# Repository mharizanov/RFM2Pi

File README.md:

RFM2Pi
======

RFM12B to Raspberry Pi board

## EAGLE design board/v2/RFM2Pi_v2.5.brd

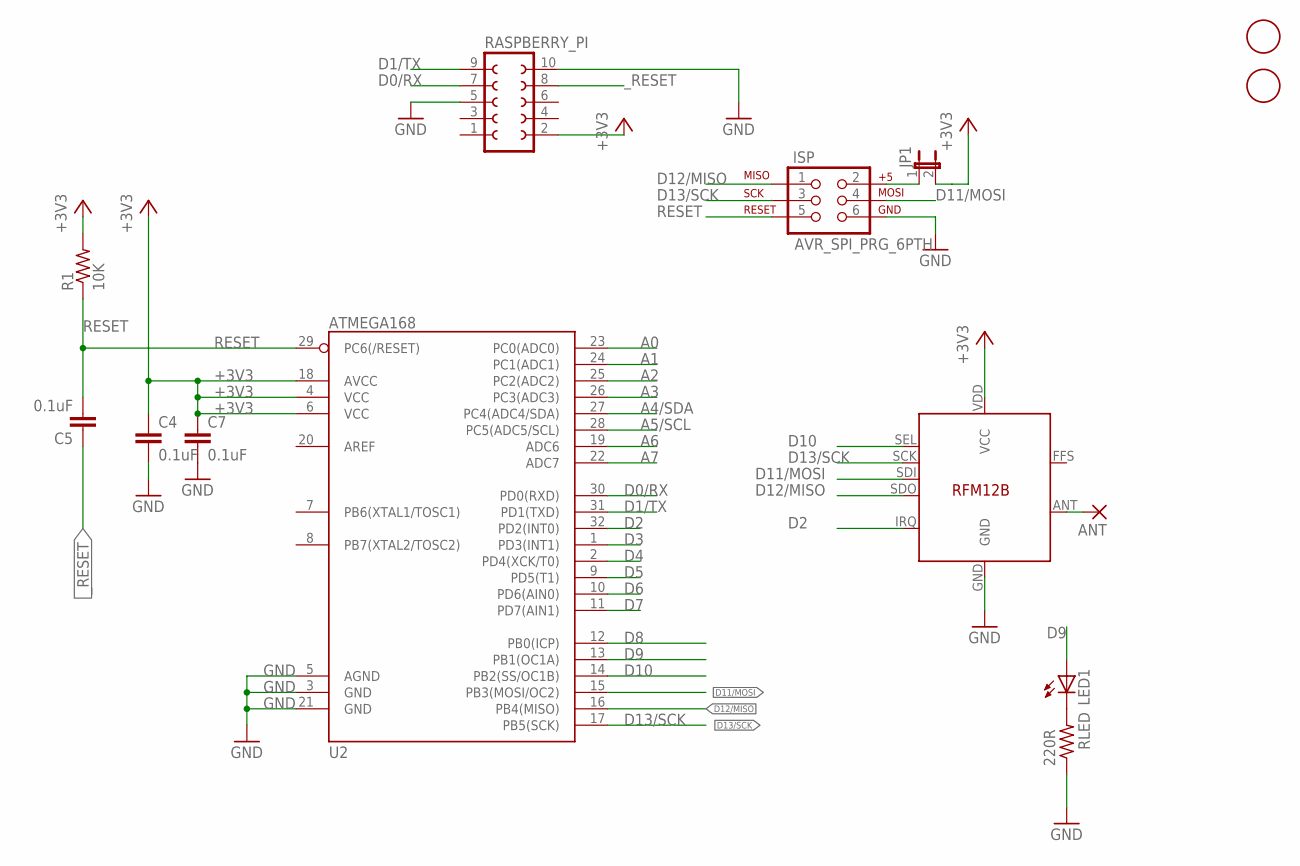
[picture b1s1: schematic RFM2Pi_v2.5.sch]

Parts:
ANT: 1,6/0,8
C4, C5, C7: 0.1uF; C0603
ISP: AVR_SPI_PRG_6PTH; 2X3
JP1: JUMPER-2PTH; 1X02
LED1: LEDSML0603; SML0603
R1: 10K; R0603
RASPBERRY_PI: FE05-2
RFM12B: RFM12B
RLED: 220R; R0603
U2: ATMEGA168; TQFP32-08
U$1, U$2: FIDUCIAL; FIDUCIAL_1MM

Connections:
+3V3: C4.1, C7.1, JP1.2, R1.2, RASPBERRY_PI.2, RFM12B.VDD (VCC), U2.4 (VCC), U2.6 (VCC), U2.18 (AVCC)
+5V: ISP.2, JP1.1
A0: U2.23 (PC0(ADC0))
A1: U2.24 (PC1(ADC1))
A2: U2.25 (PC2(ADC2))
A3: U2.26 (PC3(ADC3))
A4/SDA: U2.27 (PC4(ADC4/SDA))
A5/SCL: U2.28 (PC5(ADC5/SCL))
A6: U2.19 (ADC6)
A7: U2.22 (ADC7)
D0/RX: RASPBERRY_PI.7, U2.30 (PD0(RXD))
D1/TX: RASPBERRY_PI.9, U2.31 (PD1(TXD))
D2: RFM12B.IRQ, U2.32 (PD2(INT0))
D3: U2.1 (PD3(INT1))
D4: U2.2 (PD4(XCK/T0))
D5: U2.9 (PD5(T1))
D6: U2.10 (PD6(AIN0))
D7: U2.11 (PD7(AIN1))
D8: U2.12 (PB0(ICP))
D9: LED1.A, U2.13 (PB1(OC1A))
D10: RFM12B.SEL, U2.14 (PB2(SS/OC1B))
D11/MOSI: ISP.4, RFM12B.SDI, U2.15 (PB3(MOSI/OC2))
D12/MISO: ISP.1, RFM12B.SDO, U2.16 (PB4(MISO))
D13/SCK: ISP.3, RFM12B.SCK, U2.17 (PB5(SCK))
GND: C4.2, C7.2, ISP.6, RASPBERRY_PI.5, RASPBERRY_PI.10, RFM12B.GND, RLED.1, U2.3 (GND), U2.5 (AGND), U2.21 (GND)
unnamed: LED1.C, RLED.2
unnamed: ANT.1, RFM12B.ANT
RESET: C5.2, ISP.5, R1.1, U2.29 (PC6(/RESET))
_RESET: C5.1, RASPBERRY_PI.8

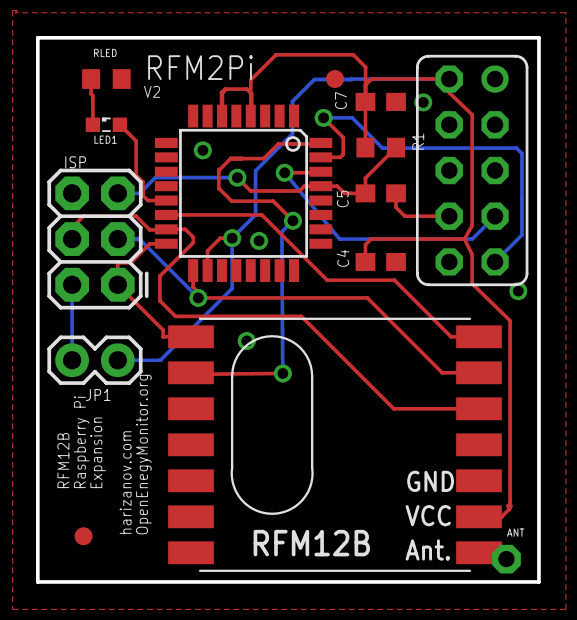
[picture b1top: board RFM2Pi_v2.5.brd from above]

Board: 2 copper layers, 27.8 x 30.2 mm, 14 parts (0 on the bottom side), 15 nets.

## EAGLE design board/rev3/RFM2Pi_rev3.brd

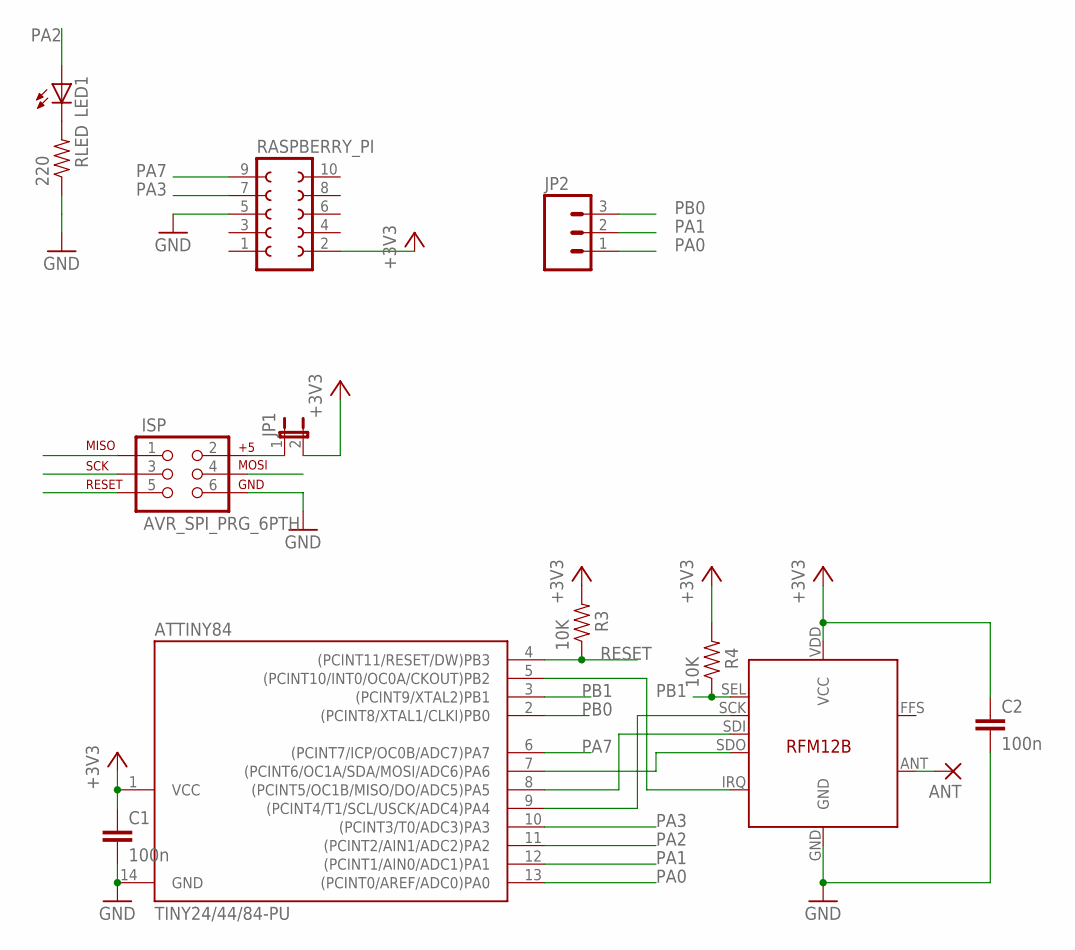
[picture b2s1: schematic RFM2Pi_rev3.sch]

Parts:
ANT: 1,6/0,8
ATTINY84: TINY24/44/84-PU; DIL14
C1, C2: 100n; C025-024X044
ISP: AVR_SPI_PRG_6PTH; 2X3
JP1: JUMPER-2PTH; 1X02
JP2: M03LOCK; 1X03_LOCK
LED1: LED5MM
R3, R4: 10K; AXIAL-0.3
RASPBERRY_PI: FE05-2
RFM12B: RFM12B
RLED: 220; AXIAL-0.3

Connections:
+3V3: ATTINY84.1 (VCC), C1.1, C2.1, JP1.2, R3.P$2 (2), R4.P$2 (2), RASPBERRY_PI.2, RFM12B.VDD (VCC)
GND: ATTINY84.14 (GND), C1.2, C2.2, ISP.6, RASPBERRY_PI.5, RFM12B.GND, RLED.P$1 (1)
MISO: ATTINY84.8 ((PCINT5/OC1B/MISO/DO/ADC5)PA5), ISP.1, RFM12B.SDI
MOSI: ATTINY84.7 ((PCINT6/OC1A/SDA/MOSI/ADC6)PA6), ISP.4, RFM12B.SDO
unnamed: ISP.2, JP1.1
unnamed: LED1.K (C), RLED.P$2 (2)
unnamed: ANT.1, RFM12B.ANT
PA0: ATTINY84.13 ((PCINT0/AREF/ADC0)PA0), JP2.1
PA1: ATTINY84.12 ((PCINT1/AIN0/ADC1)PA1), JP2.2
PA2: ATTINY84.11 ((PCINT2/AIN1/ADC2)PA2), LED1.A
PA3: ATTINY84.10 ((PCINT3/T0/ADC3)PA3), RASPBERRY_PI.7
PA7: ATTINY84.6 ((PCINT7/ICP/OC0B/ADC7)PA7), RASPBERRY_PI.9
PB0: ATTINY84.2 ((PCINT8/XTAL1/CLKI)PB0), JP2.3
PB1: ATTINY84.3 ((PCINT9/XTAL2)PB1), R4.P$1 (1), RFM12B.SEL
PB2: ATTINY84.5 ((PCINT10/INT0/OC0A/CKOUT)PB2), RFM12B.IRQ
RESET: ATTINY84.4 ((PCINT11/RESET/DW)PB3), ISP.5, R3.P$1 (1)
SCK: ATTINY84.9 ((PCINT4/T1/SCL/USCK/ADC4)PA4), ISP.3, RFM12B.SCK

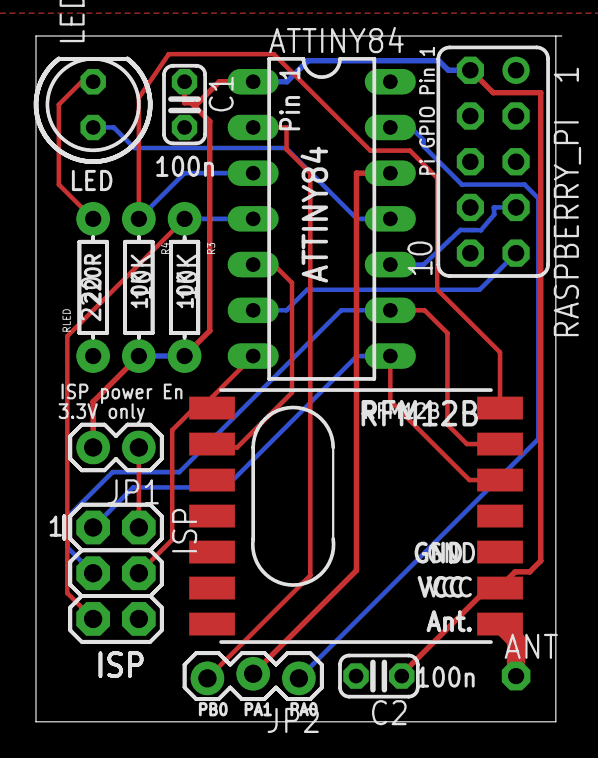
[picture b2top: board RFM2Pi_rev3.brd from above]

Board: 2 copper layers, 29.2 x 38.1 mm, 13 parts (0 on the bottom side), 17 nets.

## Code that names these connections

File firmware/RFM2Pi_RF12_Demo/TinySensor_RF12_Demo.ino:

// RF12Demo for Attiny84_RFM12b
// Configure some values in EEPROM for easy config of the RF12 later on.
// 2009-05-06 <jc@wippler.nl> http://opensource.org/licenses/mit-license.php

#include <SoftwareSerial.h>
#define rxPin 7 //PA3
#define txPin 3 //PA7

SoftwareSerial mySerial(rxPin, txPin);

/*
                     +-\/-+
               VCC  1|    |14  GND
          (D0) PB0  2|    |13  AREF (D10)
          (D1) PB1  3|    |12  PA1 (D9)
             RESET  4|    |11  PA2 (D8)
INT0  PWM (D2) PB2  5|    |10  PA3 (D7)
      PWM (D3) PA7  6|    |9   PA4 (D6)
      PWM (D4) PA6  7|    |8   PA5 (D5) PWM
                     +----+
*/


#include <JeeLib.h>
#include <util/crc16.h>
#include <util/parity.h>
#include <avr/pgmspace.h>
#include <avr/eeprom.h>

#define LED_PIN     8   

#define COLLECT 0x20 // collect mode, i.e. pass incoming without sending acks

static unsigned long now () {
    // FIXME 49-day overflow
    return millis() / 1000;
}

static void activityLed (byte on) {

    pinMode(LED_PIN, OUTPUT);
    digitalWrite(LED_PIN, on);

}

// - - - - - - - - - - - - - - - - - - - - - - - - - - - - - - - - - - - - - - -
// RF12 configuration setup code

typedef struct {
    byte nodeId;
    byte group;
//    char msg[30-4];
    word crc;
} RF12Config;

static RF12Config config;

static char cmd;
static byte value, stack[20], top, sendLen, dest, quiet;
static byte testbuf[20], testCounter;


static void saveConfig () {
    // save to EEPROM

    eeprom_write_byte(RF12_EEPROM_ADDR ,config.nodeId);
    eeprom_write_byte(RF12_EEPROM_ADDR +1 ,config.group);

    config.crc = ~0;
    config.crc = _crc16_update(config.crc, config.nodeId);     
    config.crc = _crc16_update(config.crc, config.group);        
        
    for (int i=2; i < RF12_EEPROM_SIZE-2; i++) {
        eeprom_write_byte(RF12_EEPROM_ADDR + i, 0);
        config.crc = _crc16_update(config.crc, 0);        
    }

    eeprom_write_byte(RF12_EEPROM_ADDR + RF12_EEPROM_SIZE-2 ,config.crc);
    eeprom_write_byte(RF12_EEPROM_ADDR + RF12_EEPROM_SIZE-1 ,config.crc>>8);
    
    if (!rf12_config())
        mySerial.println("config save failed");
}


char helpText1[] PROGMEM = 
    "\n"
    "Available commands:" "\n"
    "  <nn> i     - set node ID (standard node ids are 1..26)" "\n"
    "               (or enter an uppercase 'A'..'Z' to set id)" "\n"
    "  <n> b      - set MHz band (4 = 433, 8 = 868, 9 = 915)" "\n"
    "  <nnn> g    - set network group (RFM12 only allows 212, 0 = any)" "\n"
    "  <n> c      - set collect mode (advanced, normally 0)" "\n"
    "  ...,<nn> a - send data packet to node <nn>, with ack" "\n"
    "  ...,<nn> s - send data packet to node <nn>, no ack" "\n"
    "  <n> l      - turn activity LED on DIG8 on or off" "\n"
    "  <n> q      - set quiet mode (1 = don't report bad packets)" "\n"
;

static void showString (PGM_P s) {
    for (;;) {
        char c = pgm_read_byte(s++);
        if (c == 0)
            break;
        if (c == '\n')
            mySerial.print('\r');
        mySerial.print(c);
    }
}

static void showHelp () {
    showString(helpText1);
    mySerial.println("Current configuration:");
    config.nodeId = eeprom_read_byte(RF12_EEPROM_ADDR);
    config.group = eeprom_read_byte(RF12_EEPROM_ADDR + 1);

/*
    mySerial.println("EEPROM config: ");        
    uint16_t crc = ~0;
    for (uint8_t i = 0; i < RF12_EEPROM_SIZE; ++i){
        crc = _crc16_update(crc, eeprom_read_byte(RF12_EEPROM_ADDR + i));
       mySerial.print(eeprom_read_byte(RF12_EEPROM_ADDR + i),HEX);
    }
    mySerial.println("");        
    
    mySerial.print("crc:");        
    mySerial.print(crc);        
    mySerial.print(" ");            
 */
 
    byte id = config.nodeId & 0x1F;
    mySerial.print('@' + id,DEC);
    mySerial.print(" i");
    mySerial.print( id,DEC);
    if (config.nodeId & COLLECT)
         mySerial.print('*');
    
    mySerial.print(" g");
    mySerial.print(config.group,DEC);
    
    mySerial.print(" @ ");
    static word bands[4] = { 315, 433, 868, 915 };
    word band = config.nodeId >> 6;
    mySerial.print(bands[band],DEC);
    mySerial.println( " MHz ");


    rf12_config();
}

static void handleInput (char c) {
    if ('0' <= c && c <= '9')
        value = 10 * value + c - '0';
    else if (c == ',') {
        if (top < sizeof stack)
            stack[top++] = value;
        value = 0;
    } else if ('a' <= c && c <='z') {
        mySerial.print("> ");
        mySerial.print((int) value);
        mySerial.println(c);
        switch (c) {
            default:
                showHelp();
                break;
            case 'i': // set node id
                config.nodeId = (config.nodeId & 0xE0) + (value & 0x1F);
                saveConfig();
                break;
            case 'b': // set band: 4 = 433, 8 = 868, 9 = 915
                value = value == 8 ? RF12_868MHZ :
                        value == 9 ? RF12_915MHZ : RF12_433MHZ;
                config.nodeId = (value << 6) + (config.nodeId & 0x3F);
                saveConfig();
                break;
            case 'g': // set network group
                config.group = value;
                saveConfig();
                break;
            case 'c': // set collect mode (off = 0, on = 1)
                if (value)
                    config.nodeId |= COLLECT;
                else
                    config.nodeId &= ~COLLECT;
                saveConfig();
                break;
            case 'a': // send packet to node ID N, request an ack
            case 's': // send packet to node ID N, no ack
                cmd = c;
                sendLen = top;
                dest = value;
                memcpy(testbuf, stack, top);
                break;
            case 'l': // turn activity LED on or off
                activityLed(value);
                break;
            case 'q': // turn quiet mode on or off (don't report bad packets)
                quiet = value;
                break;
        }
        value = top = 0;
        memset(stack, 0, sizeof stack);
    } else if ('A' <= c && c <= 'Z') {
        config.nodeId = (config.nodeId & 0xE0) + (c & 0x1F);
        saveConfig();
    } else if (c > ' ')
        showHelp();
}

void setup() {
    
    activityLed(1);
    pinMode(rxPin, INPUT);
    pinMode(txPin, OUTPUT);
    
    // set the data rate for the NewSoftmymySerial port
    mySerial.begin(9600);
    
    mySerial.print("\n[RF12demo.Attiny84]\n\r");

    delay(2000);

    if (rf12_config()) {
        config.nodeId = eeprom_read_byte(RF12_EEPROM_ADDR);
        config.group = eeprom_read_byte(RF12_EEPROM_ADDR + 1);
    } else {
        config.nodeId = 0x81; // node A1 @ 868 MHz
        config.group = 0xD2;  //210
        rf12_initialize(config.nodeId&0x1F, config.nodeId >> 6 ,config.group);        
        saveConfig();
    }
   
    showHelp();
    activityLed(0);
}

void loop() {
    if (mySerial.available())
        handleInput(mySerial.read());

    if (rf12_recvDone() & (rf12_crc == 0) ) {
        activityLed(1);      
        byte n = rf12_len;

        if (config.group == 0) {
            mySerial.print("G ");
            mySerial.print((int) rf12_grp);
        }
        mySerial.print(' ');
        mySerial.print((int) rf12_hdr);
        for (byte i = 0; i < n; ++i) {
            mySerial.print(' ');
            mySerial.print((int) rf12_data[i]);
        }
        mySerial.println();
        
        activityLed(0);
           
        if (rf12_crc == 0) {
            activityLed(1);
            
            if (RF12_WANTS_ACK && (config.nodeId & COLLECT) == 0) {
                mySerial.println(" -> ack");
                rf12_sendStart(RF12_ACK_REPLY, 0, 0);
            }
            
            activityLed(0);
        }
    }

    if (cmd && rf12_canSend()) {
        activityLed(1);

        mySerial.print(" -> ");
        mySerial.print((int) sendLen);
        mySerial.println(" b");
        byte header = cmd == 'a' ? RF12_HDR_ACK : 0;
        if (dest)
            header |= RF12_HDR_DST | dest;
        rf12_sendStart(header, testbuf, sendLen);
        cmd = 0;

        activityLed(0);
    }
}

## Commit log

2012-10-13 initial
2012-10-15 add pre compiled RFM12 demo HEX
2012-12-01 Added option to lock RFM2Pi configuration
2012-12-01 Added compiled .hex
2012-12-22 Update firmware/RFM2Pi_RF12_Demo/TinySensor_RF12_Demo/TinySensor_RF12_Demo.ino
    Fixed brocken ACK sending
2012-12-28 update pre-compiled hex to include Martin's firmware changes
2013-01-05 Filter out unnecessary stuff and leave only NodeID
2013-01-08 undo a misfortunate fix
2013-01-08 updated to latest version
2013-01-10 Trying a fix for freezup on ACK-ing packets
2013-01-10 still fighting those lokups..
2013-01-10 adding compiled .hex
2013-02-02 Jérôme's fix
2013-02-12 Update RPi_software/perl_gateway/serial.pl
    I removed an extra closing bracket that causes fail - line 92
2013-02-21 Adding 328-based firmware
2013-02-21 Adding v2 rev 5 board eagle files
2013-02-23 pre-compiled optiboot for 8Mhz @38.5Kbps
2013-03-07 update for the LED blinking on optiboot run
2013-03-10 add combined bootloader plus RF12Demo firmware as single hex
2013-06-11 add FS20 and Kaku commands back into RFM12 demo
2013-06-11 add in remote commands into list of possible RF12 demo commands
2013-06-11 add full JeeLans RFM12 demo example - with baud rate and default RF12 settings tweaked for RFM12Pi
2013-06-11 updated pre compiled hex for full RF12 demo to work on 8mhz
2013-06-11 modify full RF12 demo so incoming msg packets match previous RF12Pi RF12 demo
2013-06-11 don't report bad packets
2013-08-23 Add -v command as per jcw
2013-08-23 Add boards.txt so it's easy to find!
2013-09-18 RFM2Pi with OLED support
2014-01-05 add updated build with latest JeeLib with RF12 bug fixes
2014-01-24 update .hex file including boot loader to use latest JeeLib with Tx fixes, stops RFM12B somtimes hang on transmission
2014-01-24 reverse stray typo :-O
2014-01-26 bug fix: packets with bad CRC were not being rejected
2014-02-16 compiled hex file for my previous Full_RFM12demo_atmega328 CRC fix
2014-04-09 Update RF12_Demo_atmega328.ino
    Increase transmit buffer sizes from 20 to 66 bytes for use by Emoncms PacketGen Modules
2014-04-10 create hex file with new packet size increase
2014-04-10 fix pre-compiled hex file using V11 JeeLib
2014-04-17 update production .hex which includes updated firmware for packetgen plus Optiboot bootloader
2014-06-12 add RFM69CW firmware for RFM12Pi
2014-06-12 add ino for RFM69CW RF12 demo
2014-06-13 strip out 'OK' set default group 210
2014-06-13 add pre-compiled hex
2014-06-13 add 'OK' back in, add LED startup indicator with delay and invert LED function
2014-06-13 add pre-compied hex for 69cw
2014-06-16 compile fix
2014-06-27 add comments changes
2014-09-08 Line 228 typo?
    Should line 228 really have this RPI console upgrade command placed here?
2014-09-10 Increase stack buffer size
